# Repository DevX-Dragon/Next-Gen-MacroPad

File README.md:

# NextGen Macropad
The Next-Gen MacroPad is a fully DIY, multi-purpose macro pad kit. It's got programmable keys, it looks cool, and most importantly — I made it. A 14-year-old made it. So if it breaks, don't be too surprised, but also it probably won't break because I tested it a bunch.

## Specifications
- 16 Programmable Keys
- 0.96 OLED Display
- Both Bluetooth and USB C connectivity
- Per Key RGB

## Layout
### KiCad

### 3D

### Assembled

## Whats inside?
- `/3D Files` : 3D Files for 3D Printing and Source Files for your own modifcations.
- `/Firmware` : Firmware for the Macro Pad (CircuitPyhton)
- `/KiCad Files` : Soruce files for KiCad for your own modifications.
- `/Images` : Previews of multiple assets
- `/Production` : Prodution files for PCB manufacturings.
- `BOM.csv` : Price Breakdown and Links

## BOM
| Product Name | Needed Quanity | Price | Additonal Notes |
| --- | --- | --- | --- |
| [PCB and PCBA](https://jlcpcb.com/) | 1 | $ 110 | 5 PCB with 2 PCBA |
| [Key Switches](https://share.temu.com/qnOeKNn7wBB) | 16 | $ 35 | A pack of 35 switches |
| [Key Caps](https://www.aliexpress.com/item/1005004525231272.html) | 16 | $ 10 | Plain Key Caps, Pack of 20 |
| [OLED Display](https://www.duino.lk/product/oled-display-0-96-inche-blue-yellow/) | 1 | $ 4 | Local Hardware Store |
| [6x6x5mm THT Push Buttons](https://www.duino.lk/product/tactile-push-button-switch-2pins-6x6x5mm/) | 2 | $ 1 | Local hardware Store |
| [SK6812 Mini E LED](https://www.aliexpress.com/item/1005008308801366.html) | 16 | $ 1 | Pack of 20 | 
| 3D Printing | 1 | $ 15 | Printing Legion |
| | **Total** | **$ 176** |

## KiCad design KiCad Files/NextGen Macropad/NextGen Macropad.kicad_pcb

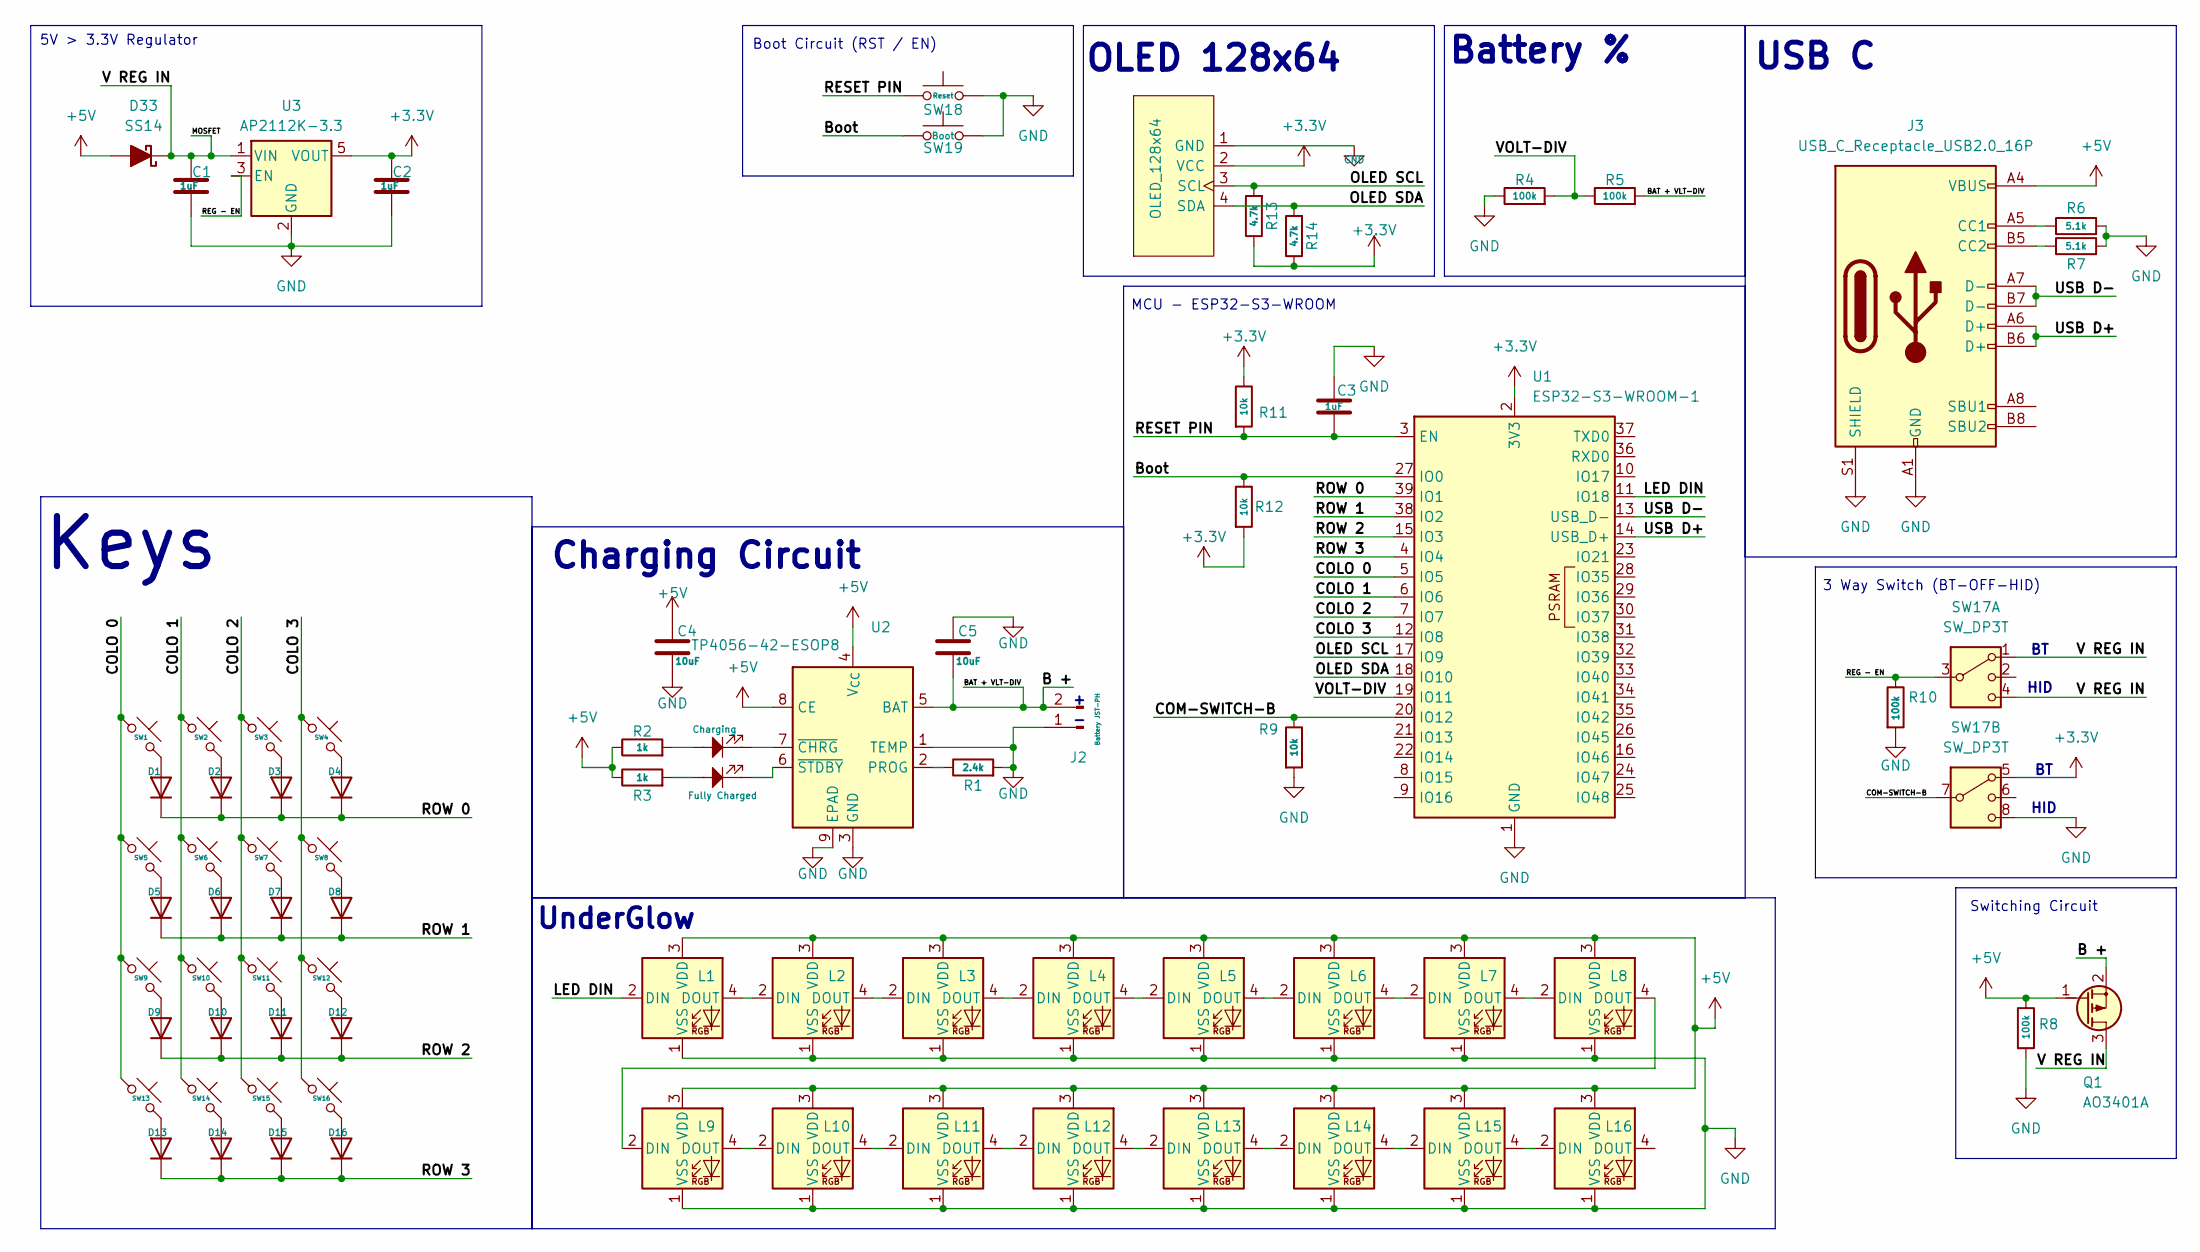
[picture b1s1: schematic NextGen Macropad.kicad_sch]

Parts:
C1, C2, C3: 1uF; C_0805_2012Metric
C4, C5: 10uF; C_0805_2012Metric
D1, D2, D3, D4, D5, D6, D7, D8, D9, D10, D11, D12, D13, D14, D15, D16: D; D_DO-35_SOD27_P7.62mm_Horizontal
D17: Charging; LED_1206_3216Metric; LCSC C2298
D18: Fully Charged; LED_1206_3216Metric; LCSC C2298
D33: SS14; D_SMA
J1: OLED_128x64
J2: Battery JST-PH; JST_PH_S2B-PH-K_1x02_P2.00mm_Horizontal
J3: USB_C_Receptacle_USB2.0_16P; USB_C_Receptacle_HRO_TYPE-C-31-M-12; LCSC C165948
L1, L2, L3, L4, L5, L6, L7, L8, L9, L10, L11, L12, L13, L14, L15, L16: SK6812; SK6812MINI-E_fixed
Q1: AO3401A; SOT-23
R1: 2.4k; R_0805_2012Metric
R2, R3: 1k; R_0805_2012Metric
R4, R5, R8, R10: 100k; R_0805_2012Metric
R6, R7: 5.1k; R_0805_2012Metric
R9, R11, R12: 10k; R_0805_2012Metric
R13, R14: 4.7k; R_0805_2012Metric
SW1, SW2, SW3, SW4, SW5, SW6, SW7, SW8, SW9, SW10, SW11, SW12, SW13, SW14, SW15, SW16: SW_Push_45deg; SW_Cherry_MX_1.00u_PCB
SW17: SW_DP3T; CL-SB-23A-11T
SW18: Reset; SW_Push_1TS009xxxx-xxxx-xxxx_6x6x5mm; LCSC C42416254
SW19: Boot; SW_Push_1TS009xxxx-xxxx-xxxx_6x6x5mm; LCSC C42416254
U1: ESP32-S3-WROOM-1
U2: TP4056-42-ESOP8; SOIC-8-1EP_3.9x4.9mm_P1.27mm_EP2.41x3.3mm_ThermalVias; LCSC C16581
U3: AP2112K-3.3; SOT-23-5; LCSC C23380830

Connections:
+3.3V: C2.1, J1.2 (VCC), R11.1, R12.2, R13.1, R14.1, SW17.5, U1.2 (3V3), U3.5 (VOUT)
+5V: C4.1, D33.2 (A), J3.A4 (VBUS), J3.A9 (VBUS), J3.B4 (VBUS), J3.B9 (VBUS), L1.3 (VDD), L2.3 (VDD), L3.3 (VDD), L4.3 (VDD), L5.3 (VDD), L6.3 (VDD), L7.3 (VDD), L8.3 (VDD), L9.3 (VDD), L10.3 (VDD), L11.3 (VDD), L12.3 (VDD), L13.3 (VDD), L14.3 (VDD), L15.3 (VDD), L16.3 (VDD), Q1.1 (G), R2.1, R3.1, R8.1, U2.4 (V_{CC}), U2.8 (CE)
/B +: C5.2, J2.2, Q1.2 (S), R5.2, U2.5 (BAT)
/Boot: R12.1, SW19.1, U1.27 (IO0)
/COLO 0: SW1.1, SW5.1, SW9.1, SW13.1, U1.5 (IO5)
/COLO 1: SW2.1, SW6.1, SW10.1, SW14.1, U1.6 (IO6)
/COLO 2: SW3.1, SW7.1, SW11.1, SW15.1, U1.7 (IO7)
/COLO 3: SW4.1, SW8.1, SW12.1, SW16.1, U1.12 (IO8)
/COM-SWITCH-B: R9.1, SW17.7, U1.20 (IO12)
/LED DIN: L1.2 (DIN), U1.11 (IO18)
/MOSFET: C1.1, D33.1 (K), Q1.3 (D), SW17.1, SW17.4, U3.1 (VIN)
/OLED SCL: J1.3 (SCL), R13.2, U1.17 (IO9)
/OLED SDA: J1.4 (SDA), R14.2, U1.18 (IO10)
/REG - EN: R10.1, SW17.3, U3.3 (EN)
/RESET PIN: C3.2, R11.2, SW18.1, U1.3 (EN)
/ROW 0: D1.1 (K), D2.1 (K), D3.1 (K), D4.1 (K), U1.39 (IO1)
/ROW 1: D5.1 (K), D6.1 (K), D7.1 (K), D8.1 (K), U1.38 (IO2)
/ROW 2: D9.1 (K), D10.1 (K), D11.1 (K), D12.1 (K), U1.15 (IO3)
/ROW 3: D13.1 (K), D14.1 (K), D15.1 (K), D16.1 (K), U1.4 (IO4)
/USB D+: J3.A6 (D+), J3.B6 (D+), U1.14 (USB_D+)
/USB D-: J3.A7 (D-), J3.B7 (D-), U1.13 (USB_D-)
/VOLT-DIV: R4.2, R5.1, U1.19 (IO11)
GND: C1.2, C2.2, C3.1, C4.2, C5.1, J1.1 (GND), J2.1, J3.A1 (GND), J3.A12 (GND), J3.B1 (GND), J3.B12 (GND), J3.S1 (SHIELD), L1.1 (VSS), L2.1 (VSS), L3.1 (VSS), L4.1 (VSS), L5.1 (VSS), L6.1 (VSS), L7.1 (VSS), L8.1 (VSS), L9.1 (VSS), L10.1 (VSS), L11.1 (VSS), L12.1 (VSS), L13.1 (VSS), L14.1 (VSS), L15.1 (VSS), L16.1 (VSS), R1.2, R4.1, R6.2, R7.2, R8.2, R9.2, R10.2, SW17.8, SW18.2, SW19.2, U1.1 (GND), U1.40 (GND), U1.41 (GND), U2.1 (TEMP), U2.3 (GND), U2.9 (EPAD), U3.2 (GND)
unnamed: D1.2 (A), SW1.2
unnamed: D2.2 (A), SW2.2
unnamed: D3.2 (A), SW3.2
unnamed: D4.2 (A), SW4.2
unnamed: D5.2 (A), SW5.2
unnamed: D6.2 (A), SW6.2
unnamed: D7.2 (A), SW7.2
unnamed: D8.2 (A), SW8.2
unnamed: D9.2 (A), SW9.2
unnamed: D10.2 (A), SW10.2
unnamed: D11.2 (A), SW11.2
unnamed: D12.2 (A), SW12.2
unnamed: D13.2 (A), SW13.2
unnamed: D14.2 (A), SW14.2
unnamed: D15.2 (A), SW15.2
unnamed: D16.2 (A), SW16.2
unnamed: D17.2, R2.2
unnamed: D18.2, R3.2
unnamed: J3.A5 (CC1), R6.1
unnamed: J3.B5 (CC2), R7.1
unnamed: L1.4 (DOUT), L2.2 (DIN)
unnamed: L2.4 (DOUT), L3.2 (DIN)
unnamed: L3.4 (DOUT), L4.2 (DIN)
unnamed: L4.4 (DOUT), L5.2 (DIN)
unnamed: L5.4 (DOUT), L6.2 (DIN)
unnamed: L6.4 (DOUT), L7.2 (DIN)
unnamed: L7.4 (DOUT), L8.2 (DIN)
unnamed: L8.4 (DOUT), L9.2 (DIN)
unnamed: L9.4 (DOUT), L10.2 (DIN)
unnamed: L10.4 (DOUT), L11.2 (DIN)
unnamed: L11.4 (DOUT), L12.2 (DIN)
unnamed: L12.4 (DOUT), L13.2 (DIN)
unnamed: L13.4 (DOUT), L14.2 (DIN)
unnamed: L14.4 (DOUT), L15.2 (DIN)
unnamed: L15.4 (DOUT), L16.2 (DIN)
unnamed: R1.1, U2.2 (PROG)
unnamed: D17.1, U2.7 (~CHRG)
unnamed: D18.1, U2.6 (~STDBY)

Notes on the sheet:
3 Way Switch (BT-OFF-HID)
MCU - ESP32-S3-WROOM
Boot Circuit (RST / EN)
Switching Circuit
OLED 128x64
UnderGlow
HID
Charging Circuit
5V > 3.3V Regulator
USB C
Keys
Battery %

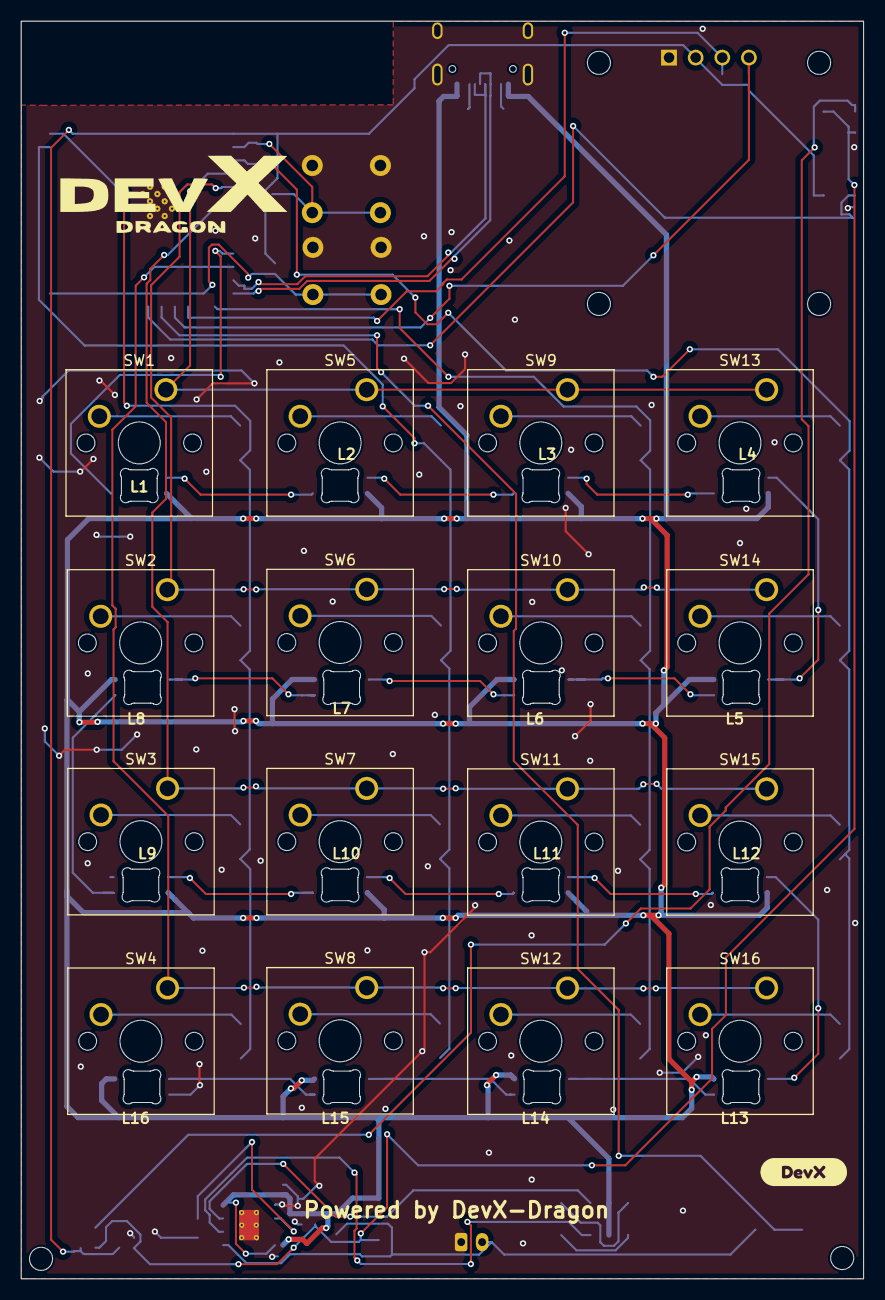
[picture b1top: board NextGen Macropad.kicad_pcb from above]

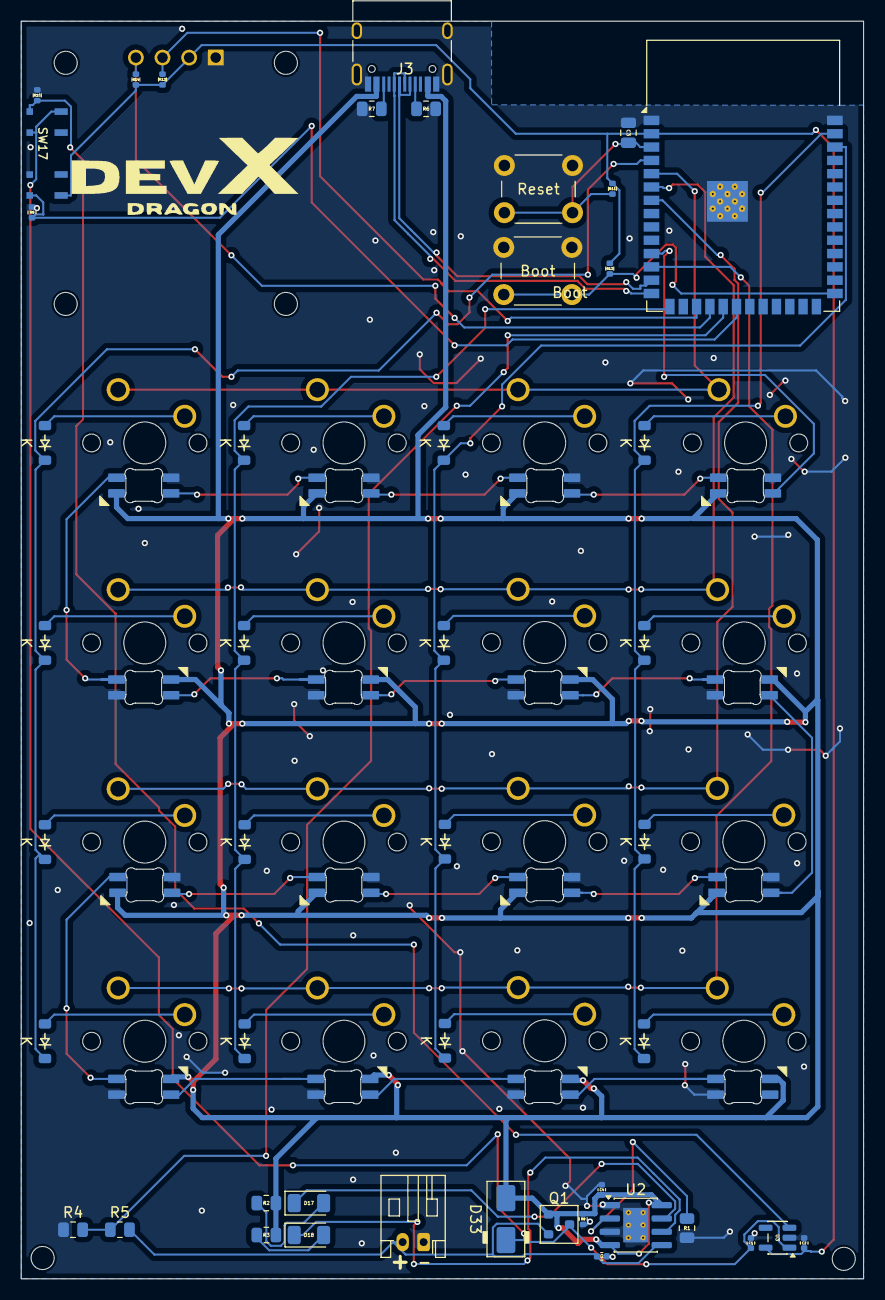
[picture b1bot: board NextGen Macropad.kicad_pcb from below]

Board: 2 copper layers, 80.3 x 119.9 mm, 81 parts (47 on the bottom side), 61 nets.

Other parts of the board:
kibuzzard-69BEA4AE: G***; kibuzzard-69BEA4AE

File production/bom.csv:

Designator,Footprint,Quantity,Value,LCSC Part #
"C1, C2",0402,2,1uF,
C3,0805,1,1uF,
"C4, C5",0402,2,10uF,
"D1, D10, D11, D12, D13, D14, D15, D16, D2, D3, D4, D5, D6, D7, D8, D9",Diode_SOD-123,16,D,
D17,1206,1,Charging,C2298
D18,1206,1,Fully Charged,C2298
D33,D_SMA,1,SS14,
J1,OLED_128x64,1,OLED_128x64,
J2,JST_PH_S2B-PH-K_1x02_P2.00mm_Horizontal,1,Battery JST-PH,
J3,USB_C_Receptacle_HRO_TYPE-C-31-M-12,1,USB_C_Receptacle_USB2.0_16P,C165948
"L1, L10, L11, L12, L13, L14, L15, L16, L2, L3, L4, L5, L6, L7, L8, L9",SK6812MINI-E_fixed,16,SK6812,
Q1,SOT-23,1,AO3401A,
R1,0805,1,2.4k,
"R10, R8",0402,2,100k,
"R11, R12, R9",0402,3,10k,
"R13, R14",0402,2,4.7k,
"R2, R3",0805,2,1k,
"R4, R5",0805,2,100k,
"R6, R7",0805,2,5.1k,
"SW1, SW10, SW11, SW12, SW13, SW14, SW15, SW16, SW2, SW3, SW4, SW5, SW6, SW7, SW8, SW9",SW_Cherry_MX_1.00u_PCB,16,SW_Push_45deg,
SW17,CL-SB-23A-11T,1,SW_DP3T,
SW18,SW_PUSH_6mm,1,Reset,C42416254
SW19,SW_PUSH_6mm,1,Boot,C42416254
U1,ESP32-S3-WROOM-1,1,ESP32-S3-WROOM-1,
U2,SOIC-8-1EP_3.9x4.9mm_P1.27mm_EP2.41x3.3mm_ThermalVias,1,TP4056-42-ESOP8,C16581
U3,SOT-23-5,1,AP2112K-3.3,C23380830

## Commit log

2026-03-17 Initial KiCad Upload
2026-03-18 Uploading KiCad + Images + Production 180326-1005
2026-03-18 Fixing Dir
2026-03-18 KiCad Update
2026-03-19 Fix PCB + Add BOM
2026-03-20 New PCB Layout
2026-03-20 more images
2026-03-21 KiCad Change
2026-03-21 Firmware Push v1
2026-03-21 Firmware v1 210326-900
2026-03-21 Firmware push v2 - 210326-904
2026-03-21 3D Changes + Images 210326-923
2026-03-21 Folder Structure 210326-933
2026-03-21 readme
2026-03-21 source file fix 210326-942
2026-03-21 3D fix 210326-950
2026-03-22 git ignore
